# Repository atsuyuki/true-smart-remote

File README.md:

# True Smart Remote

## What's This?
大量のボタンに埋め尽くされたTVリモコンからの解放を目指すスマートデバイスです。

## ToDo
- ハードウェア
    - [ ] 回路を設計する
    - [ ] 基板を設計する
    - [ ] ケースを作る
- ソフトウェア
    - [ ] プログラムを書く
        - [x] Rust
        - [ ] Arduino
        - Circuit Python（起動が遅いので使わないことにした）
        - [ ] Micro Python
    - [ ] ドキュメントを書く（READMEもちゃんと書く）
- [ ] キット化

## プロジェクト進捗状況
最新の進捗状況は[こちらのTwitterスレッド](https://twitter.com/aaa_tu/status/1522934147097841664?s=20&t=mgQVpbaO2x_IwUvTjbvjew)を参照してください。

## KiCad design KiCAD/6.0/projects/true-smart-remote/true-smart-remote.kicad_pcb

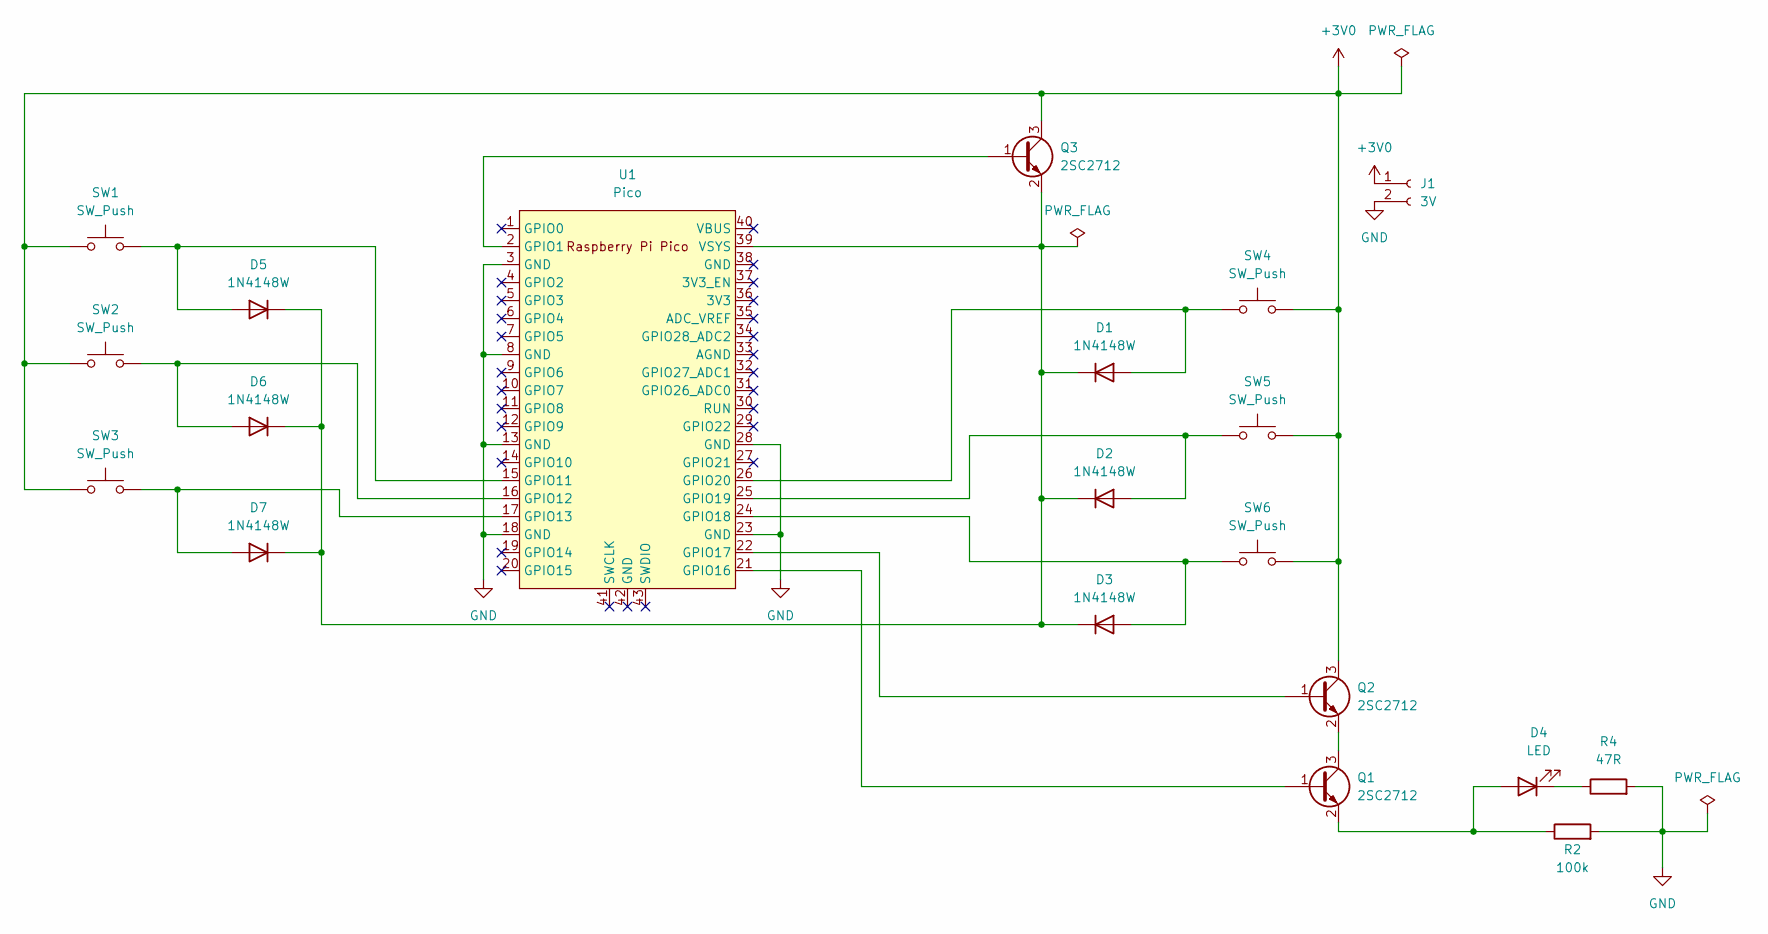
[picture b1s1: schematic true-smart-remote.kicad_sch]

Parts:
D1, D2, D3, D5, D6, D7: 1N4148W; D_SOD-123
D4: LED; LED_D3.0mm
J1: 3V; PinHeader_1x02_P2.54mm_Vertical
Q1, Q2, Q3: 2SC2712; SC-59_Handsoldering
R2: 100k; R_0603_1608Metric_Pad0.98x0.95mm_HandSolder
R4: 47R; R_0603_1608Metric_Pad0.98x0.95mm_HandSolder
SW1, SW2, SW3, SW4, SW5, SW6: SW_Push; Kailh_socket_MX_optional
U1: Pico; RPi_Pico_SMD_TH

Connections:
+3V0: J1.1, Q2.3 (C), Q3.3 (C), SW1.2, SW2.2, SW3.2, SW4.2, SW5.2, SW6.2
GND: J1.2, R2.2, R4.2, U1.3 (GND), U1.8 (GND), U1.13 (GND), U1.18 (GND), U1.23 (GND), U1.28 (GND)
unnamed: D1.1 (K), D2.1 (K), D3.1 (K), D5.1 (K), D6.1 (K), D7.1 (K), Q3.2 (E), U1.39 (VSYS)
unnamed: D1.2 (A), SW4.1, U1.26 (GPIO20)
unnamed: D2.2 (A), SW5.1, U1.25 (GPIO19)
unnamed: D3.2 (A), SW6.1, U1.24 (GPIO18)
unnamed: D4.1 (K), R4.1
unnamed: D4.2 (A), Q1.2 (E), R2.1
unnamed: D5.2 (A), SW1.1, U1.15 (GPIO11)
unnamed: D6.2 (A), SW2.1, U1.16 (GPIO12)
unnamed: D7.2 (A), SW3.1, U1.17 (GPIO13)
unnamed: Q1.1 (B), U1.21 (GPIO16)
unnamed: Q1.3 (C), Q2.2 (E)
unnamed: Q2.1 (B), U1.22 (GPIO17)
unnamed: Q3.1 (B), U1.2 (GPIO1)

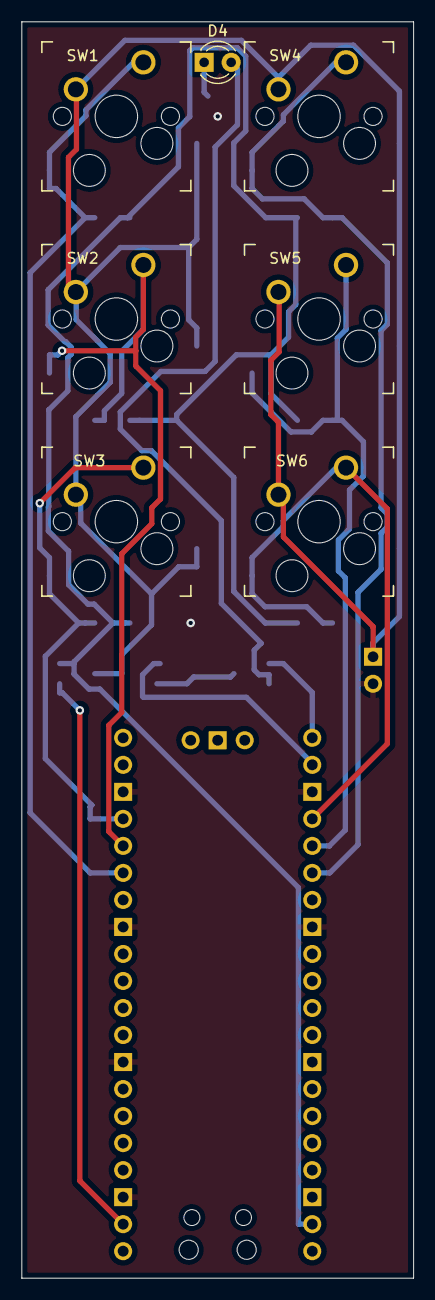
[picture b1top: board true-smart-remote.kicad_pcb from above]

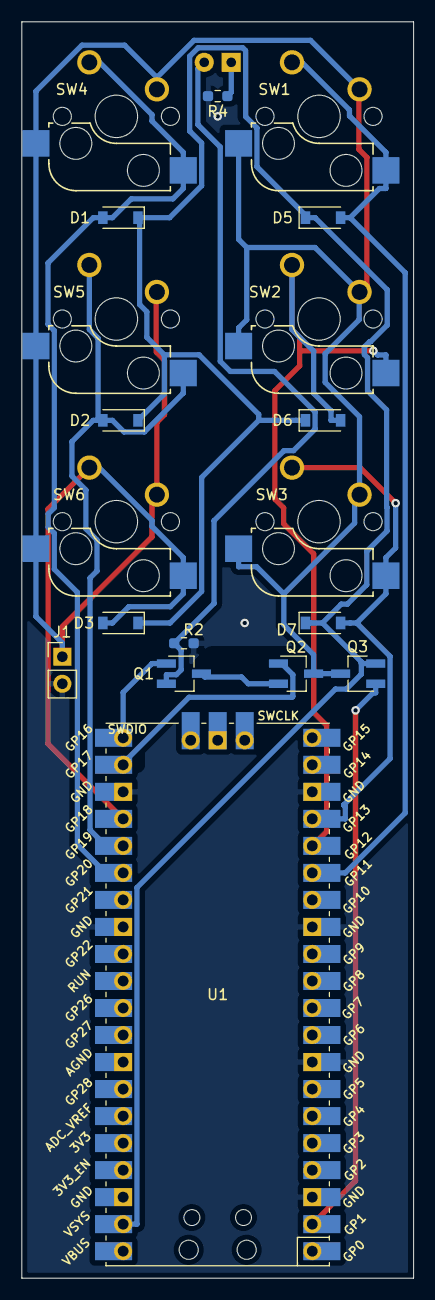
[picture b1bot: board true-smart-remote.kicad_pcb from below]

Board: 2 copper layers, 36.8 x 118.1 mm, 20 parts (13 on the bottom side), 15 nets.

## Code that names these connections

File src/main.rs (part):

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use embedded_hal::digital::v2::{InputPin, OutputPin};
use panic_reset as _;
use rp2040_hal::{
    gpio::{bank0::Gpio16, Output, Pin, PushPull},
    Clock, Watchdog,
};

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        rp2040_hal::gpio::Pins::new(pac.IO_BANK0, pac.PADS_BANK0, sio.gpio_bank0, &mut pac.RESETS);

    let mut led_pin = pins.gpio25.into_push_pull_output();
    let mut power_pin = pins.gpio1.into_push_pull_output();

    // 諸々やる前に自己保持をかけておく
    led_pin.set_high().unwrap();
    power_pin.set_high().unwrap();

    let mut pwm_pin = pins.gpio17.into_push_pull_output();
    let mut ir_pin = pins.gpio16.into_push_pull_output();

    //    pwm_pin.set_drive_strength(rp2040_hal::gpio::OutputDriveStrength::TwelveMilliAmps);
    //    ir_pin.set_drive_strength(rp2040_hal::gpio::OutputDriveStrength::TwelveMilliAmps);

    let button_4 = pins.gpio11.into_pull_down_input();
    let button_5 = pins.gpio12.into_pull_down_input();
    let button_6 = pins.gpio13.into_pull_down_input();
    let button_1 = pins.gpio20.into_pull_down_input();
    let button_2 = pins.gpio19.into_pull_down_input();
    let button_3 = pins.gpio18.into_pull_down_input();

    // PWMの参考 : https://github.com/ac100v/pico-blink-pwm/blob/main/src/main.rs
    let pwm_slices = Slices::new(pac.PWM, &mut pac.RESETS);
    // RP2040のPWMは8つのスライスに分かれていて、各スライスが2つのピンに対応している。
    // GPIO17 はPWM0のチャネルB (RP2040 Datasheet 4.5.2)
    let mut pwm = pwm_slices.pwm0;
    pwm.set_ph_correct();
    pwm.enable();
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fn send_if_pressed<PIN: InputPin>(
    button: &PIN,
    command: &[u16],
    ir_pin: &mut Pin<Gpio16, Output<PushPull>>,
    delay: &mut Delay,
) {
    if button.is_high().ok().unwrap() {
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
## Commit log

2022-08-13 ボタン入力を読みとって条件分岐するとこまでできた。
    Rustむずかしいな🤔
2022-08-15 PWMで38kHz変調をかけるようにしてみた。
    PWMの扱いがまだよくわかってないので、惜しくも38.017kHz
2022-08-15 LEDドライブ電流を4mA→12mAに変更した
    本当にそうなってるのかは謎
2022-08-16 Refactor the command sending logic into its own function
2022-08-16 Change the commands to be u16 arrays instead of u32
2022-08-16 Refactor the command sending logic into its own function (#1)
    * Refactor the command sending logic into its own function
    * Change the commands to be u16 arrays instead of u32
2022-08-16 Add github actions files for Rust
2022-08-16 Add github actions files for Rust (#2)
2022-08-16 自己保持をかけるタイミングをPin設定直後に早めた。
2022-10-09 KiCADのプロジェクトファイルを追加した
2023-02-20 Update ToDo
